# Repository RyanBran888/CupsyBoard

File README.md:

# CupsyBoard
Blinky board for stasis but its cupsy

heres my pcb!!!
its a chasracter from yugioh and it blinks and its a board!

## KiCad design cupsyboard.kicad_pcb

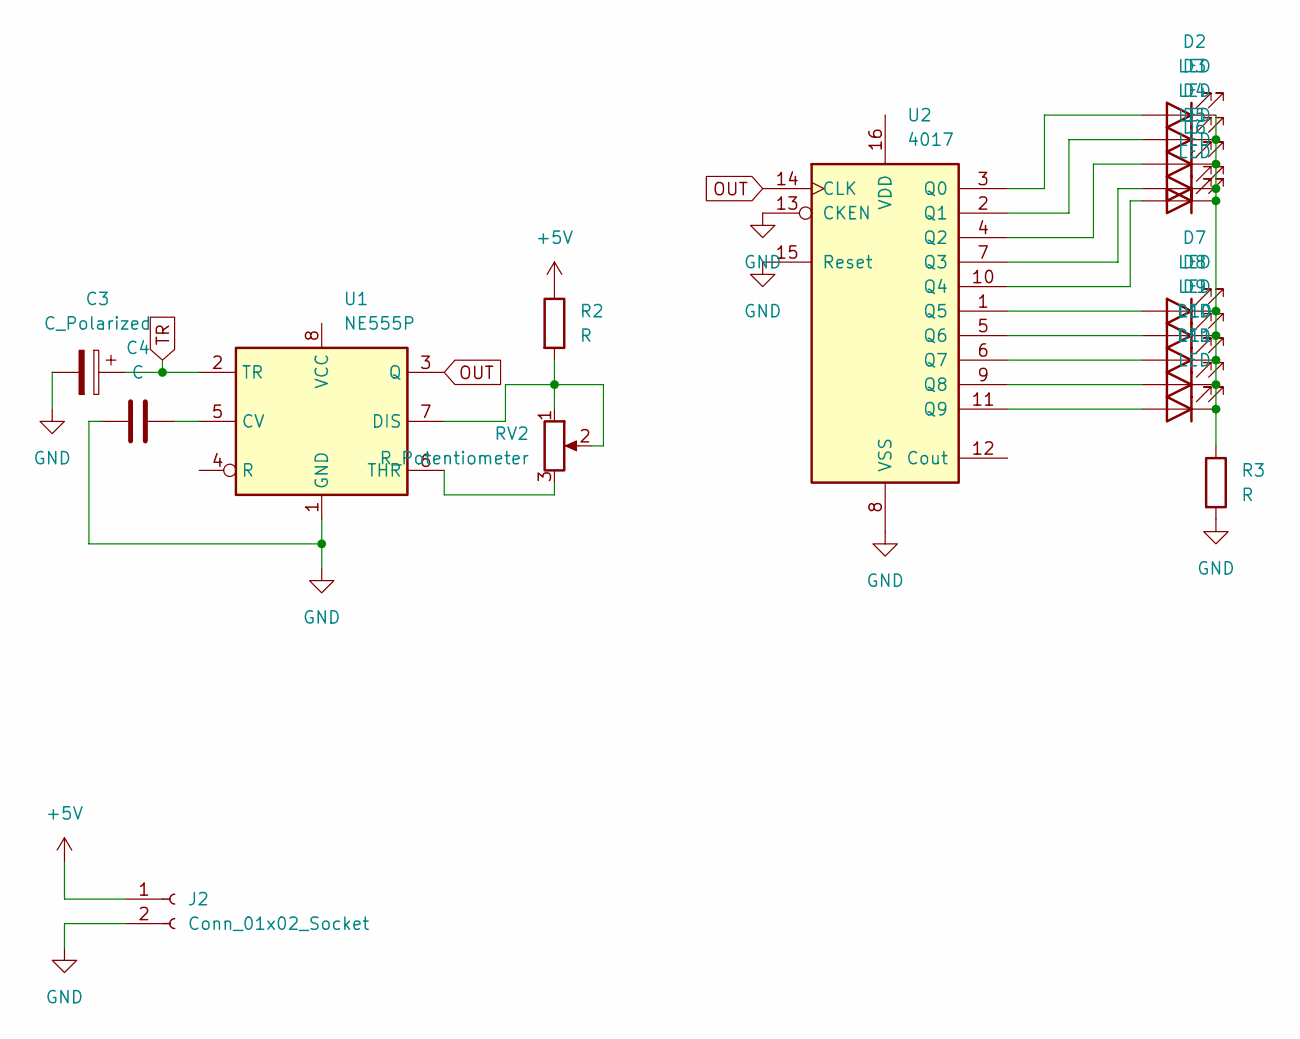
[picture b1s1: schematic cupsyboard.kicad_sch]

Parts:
C3: C_Polarized; C_Disc_D7.5mm_W2.5mm_P5.00mm
C4: C; CP_Radial_D5.0mm_P2.00mm
D2, D3, D4, D5, D6, D7, D8, D9, D10, D11: LED; LED_D3.0mm
J2: Conn_01x02_Socket; PinHeader_1x02_P2.54mm_Vertical
R2, R3: R; R_Axial_DIN0207_L6.3mm_D2.5mm_P7.62mm_Horizontal
RV2: R_Potentiometer; Potentiometer_Vishay_T93YA_Vertical
U1: NE555P; DIP-8_W7.62mm
U2: 4017; N16

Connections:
+5V: J2.1, R2.1
GND: C3.2, C4.1, J2.2, R3.2, U1.1 (GND), U2.8 (VSS), U2.13 (CKEN), U2.15 (Reset)
unnamed: D2.2 (A), U2.3 (Q0)
unnamed: D3.2 (A), U2.2 (Q1)
unnamed: D4.2 (A), U2.4 (Q2)
unnamed: D5.2 (A), U2.7 (Q3)
unnamed: D6.2 (A), U2.10 (Q4)
unnamed: D7.2 (A), U2.1 (Q5)
unnamed: D8.2 (A), U2.5 (Q6)
unnamed: D9.2 (A), U2.6 (Q7)
unnamed: D10.2 (A), U2.9 (Q8)
unnamed: D2.1 (K), D3.1 (K), D4.1 (K), D5.1 (K), D6.1 (K), D7.1 (K), D8.1 (K), D9.1 (K), D10.1 (K), D11.1 (K), R3.1
unnamed: D11.2 (A), U2.11 (Q9)
unnamed: C4.2, U1.5 (CV)
unnamed: R2.2, RV2.1, RV2.2, U1.7 (DIS)
unnamed: RV2.3, U1.6 (THR)
OUT: U1.3 (Q), U2.14 (CLK)
TR: C3.1, U1.2 (TR)

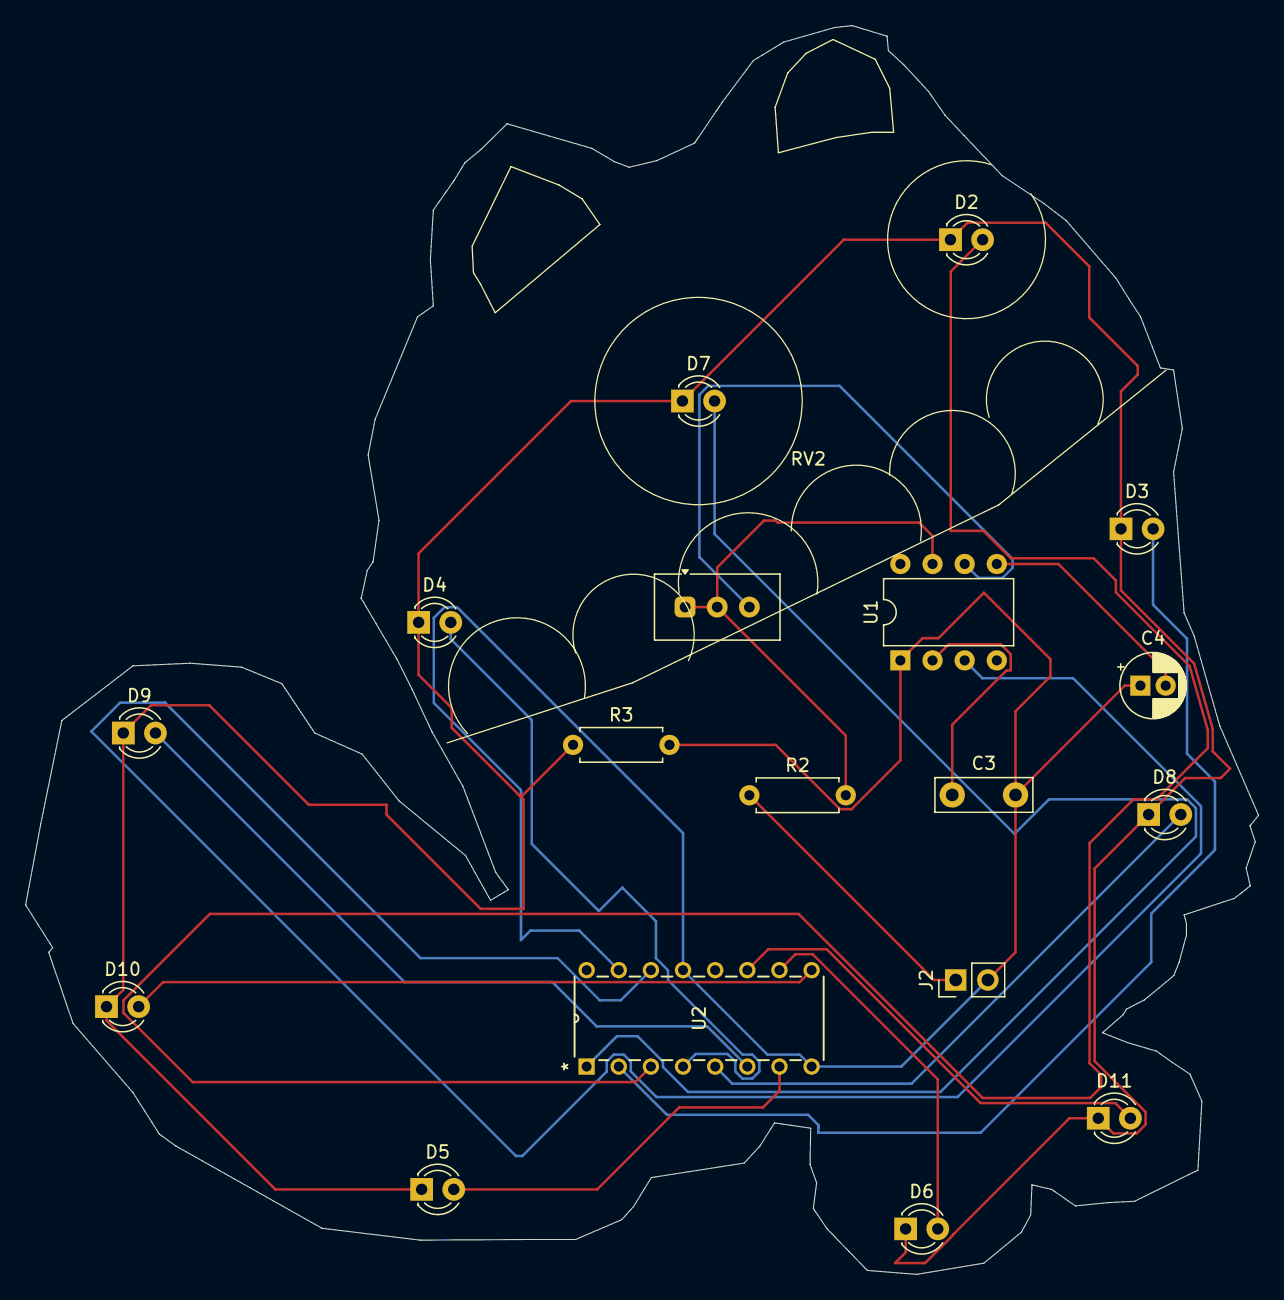
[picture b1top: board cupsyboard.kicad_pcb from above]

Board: 2 copper layers, 97.4 x 98.7 mm, 18 parts (0 on the bottom side), 18 nets.

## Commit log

2026-04-08 Update README with PCB image and description
    Added an image and description of the PCB.
